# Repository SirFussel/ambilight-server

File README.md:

# Custom Ambilight using Raspberry Pi 3
## Hardware
- Raspberry Pi 3 or higher
- USB framegrabber
- WS2801 LED stripes
- HDPC compatible HDMI splitter
- Power supply
- Wires and cables
## Software
- Hyperion
## Additional Features
- Temperature controlled case using fan
- Blind service to disable the stripes when TV is off
## Pi Configuration
### WIFI configuration
1. Add following lines to ```/etc/network/interfaces``` in order to disable WIFI power save mode:
    ```
    allow-hotplug wlan0
    iface wlan0 inet manual
    post-up iw wlan0 set power_save off
    ```
2. Make sure ```/etc/wpa_supplicant/wpa_supplicant.conf``` looks similar to this and replace the placeholders:
    ```
    ctrl_interface=DIR=/var/run/wpa_supplicant GROUP=netdev
    update_config=1
    country=DE

    network={
            ssid="<ssid>"
            psk="<password>"
    }
    ```
    You can do this by using ```sudo wpa_passphrase "<ssid>" "<password>" >> /etc/wpa_supplicant/wpa_supplicant.conficant.conf``` instead of manually adding it to the file.
3. Restart WIFI by using ```sudo ifconfig wlan0 down``` and ```sudo ifconfig wlan0 up``` afterwards.
### Add services
1. Add a file to ```/etc/systems/system/``` folder and make sure its extension is ```.service```. Its content looks similar to:
    ```
    [Unit]
    Description=Temperature control service
    After=multi-user.target
    [Service]
    Type=simple
    Restart=always
    ExecStart=/usr/bin/python3 /home/pi/tempcontrol.py
    [Install]
    WantedBy=multi-user.target
    ```
2. Register the service using ```sudo service enable <servicename>.service```
3. Run the service using ```sudo service start <servicename>.service```

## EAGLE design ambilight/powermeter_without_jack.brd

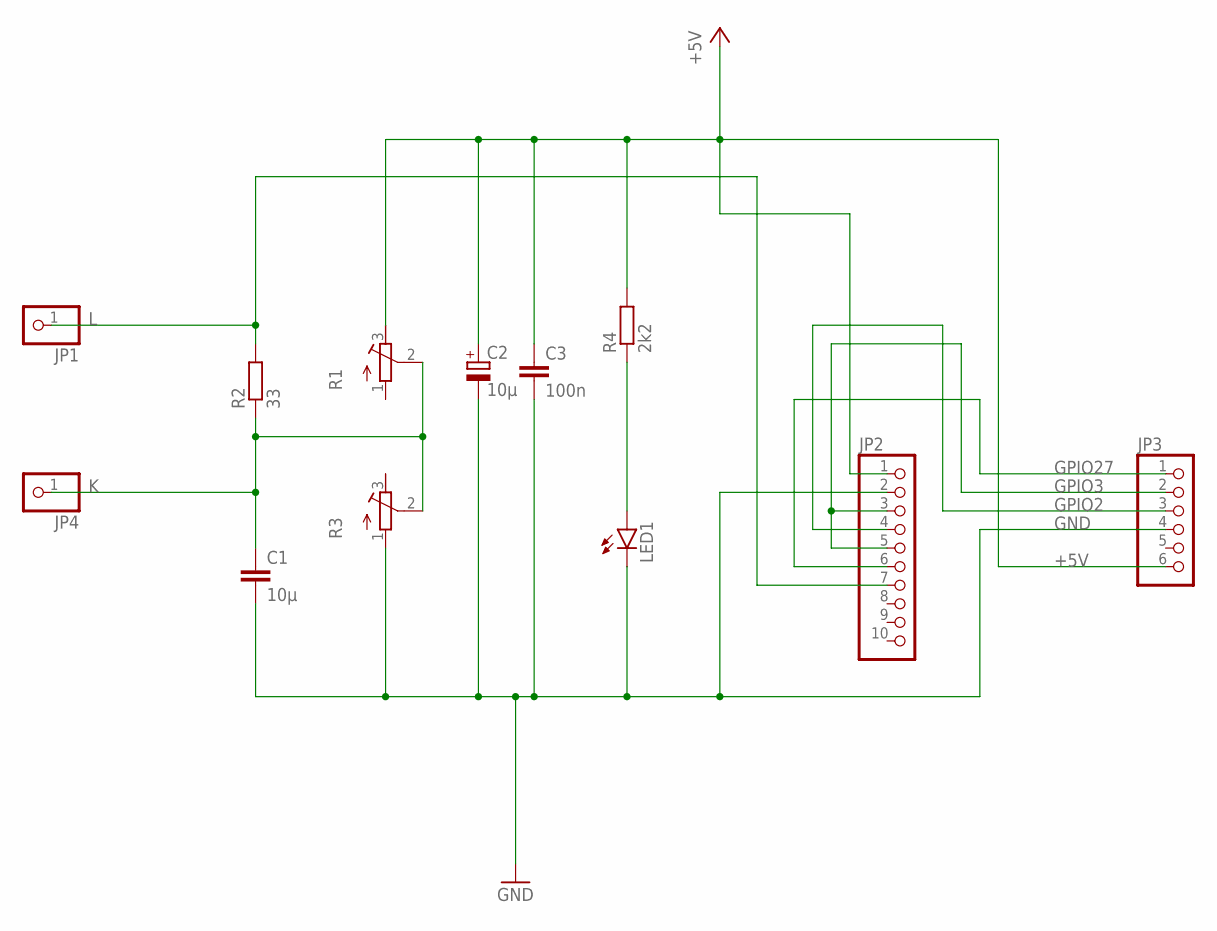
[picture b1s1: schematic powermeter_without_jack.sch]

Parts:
C1: 10µ; C075-052X106
C2: 10µ; E5-5
C3: 100n; C050-025X075
JP1, JP4: PINHD-1X1; 1X01
JP2: PINHD-1X10; 1X10
JP3: PINHD-1X6; 1X06
LED1: LED3MM
R1, R3: R-TRIMM3296W; RTRIM3296W
R2: 33; 0411/15
R4: 2k2; 0207/10

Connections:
+5V: C2.+, C3.1, JP2.1, JP3.6, R1.3 (E), R4.2
GND: C1.2, C2.-, C3.2, JP2.2, JP3.4, LED1.K (C), R3.1 (A)
GPIO2: JP2.4, JP3.3
GPIO3: JP2.3, JP2.5, JP3.2
GPIO27: JP2.6, JP3.1
K: C1.1, JP4.1, R1.2 (S), R2.1, R3.2 (S)
L: JP1.1, JP2.7, R2.2
unnamed: LED1.A, R4.1

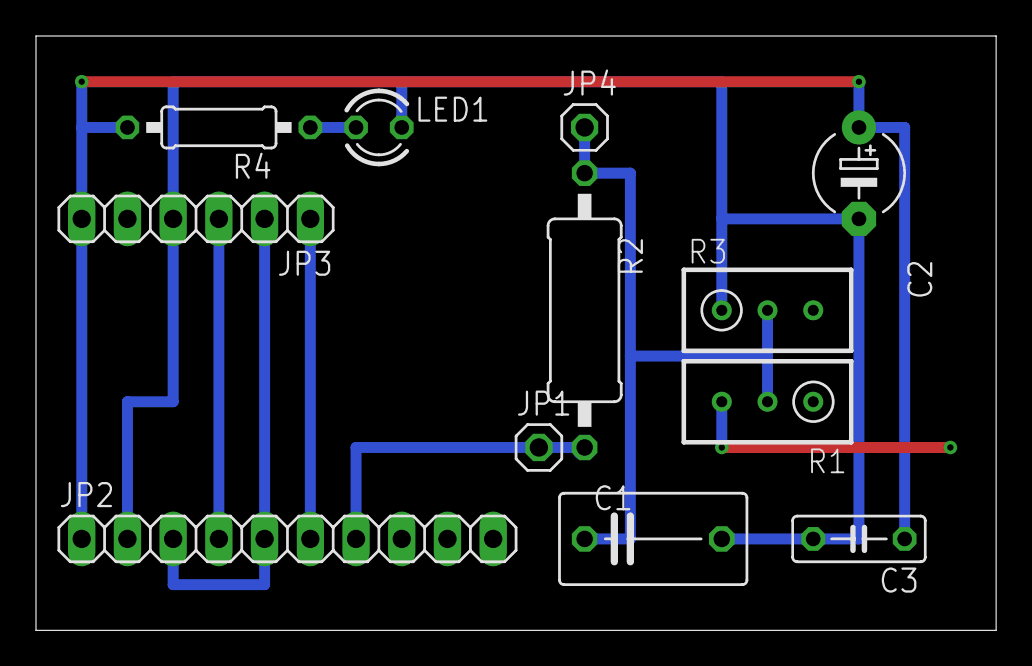
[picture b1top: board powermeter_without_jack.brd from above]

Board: 2 copper layers, 53.3 x 33.0 mm, 12 parts (0 on the bottom side), 8 nets.

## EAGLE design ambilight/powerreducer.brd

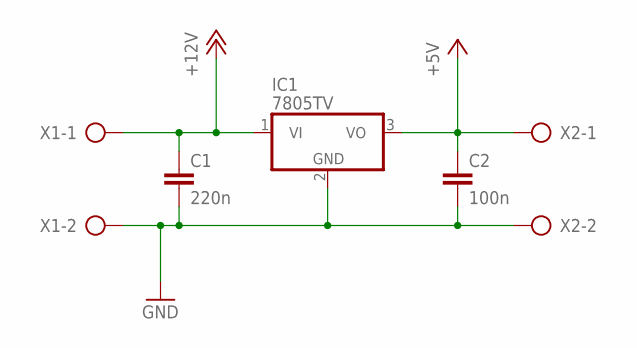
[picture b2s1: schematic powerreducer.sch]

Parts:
C1: 220n; C050-025X075
C2: 100n; C050-025X075
IC1: 7805TV; TO220V
X1, X2: AK300/2

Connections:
+5V: C2.1, IC1.3 (VO), X2.1
+12V: C1.1, IC1.1 (VI), X1.1
GND: C1.2, C2.2, IC1.2 (GND), X1.2, X2.2

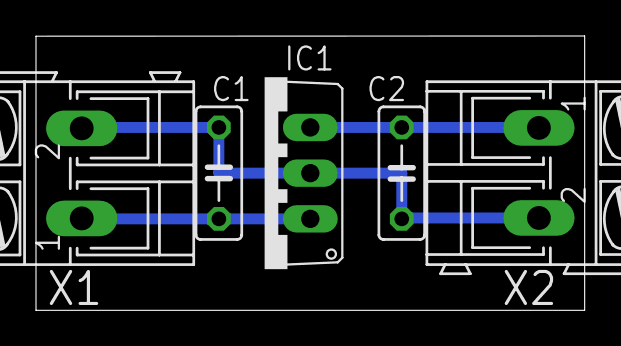
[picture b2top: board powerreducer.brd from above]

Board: 2 copper layers, 30.5 x 15.2 mm, 5 parts (0 on the bottom side), 3 nets.

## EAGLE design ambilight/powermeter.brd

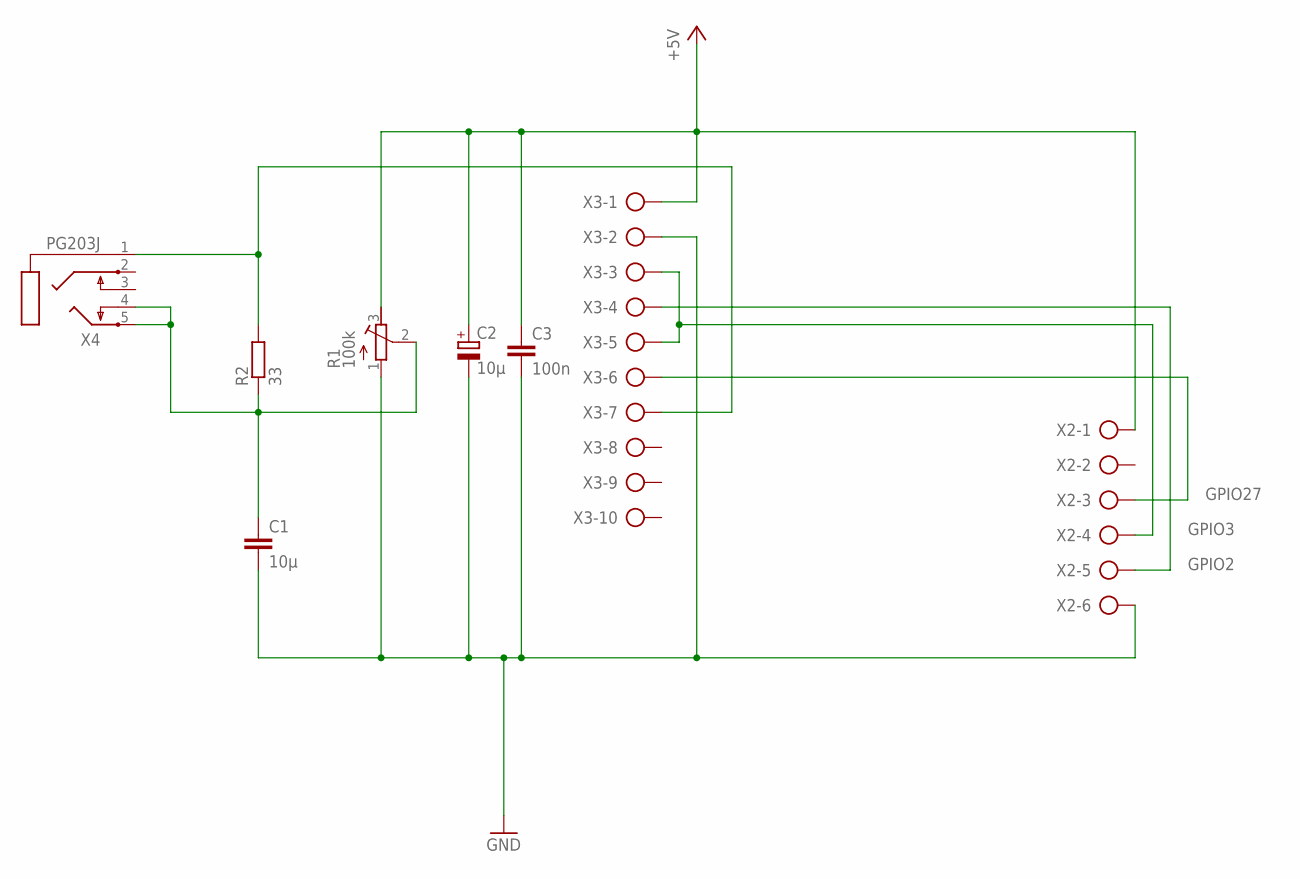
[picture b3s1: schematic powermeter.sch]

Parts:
C1: 10µ; C050-025X075
C2: 10µ; E5-10,5
C3: 100n; C050-025X075
R1: 100k; RTRIM64W
R2: 33; 0309/12
X2: AK300/6
X3: AK300/10
X4: PG203J

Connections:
+5V: C2.+, C3.1, R1.3 (E), X2.1, X3.1
GND: C1.2, C2.-, C3.2, R1.1 (A), X2.6, X3.2
GPIO2: X2.5, X3.4
GPIO3: X2.4, X3.3, X3.5
GPIO27: X2.3, X3.6
unnamed: R2.2, X3.7, X4.1
unnamed: C1.1, R1.2 (S), R2.1, X4.4, X4.5

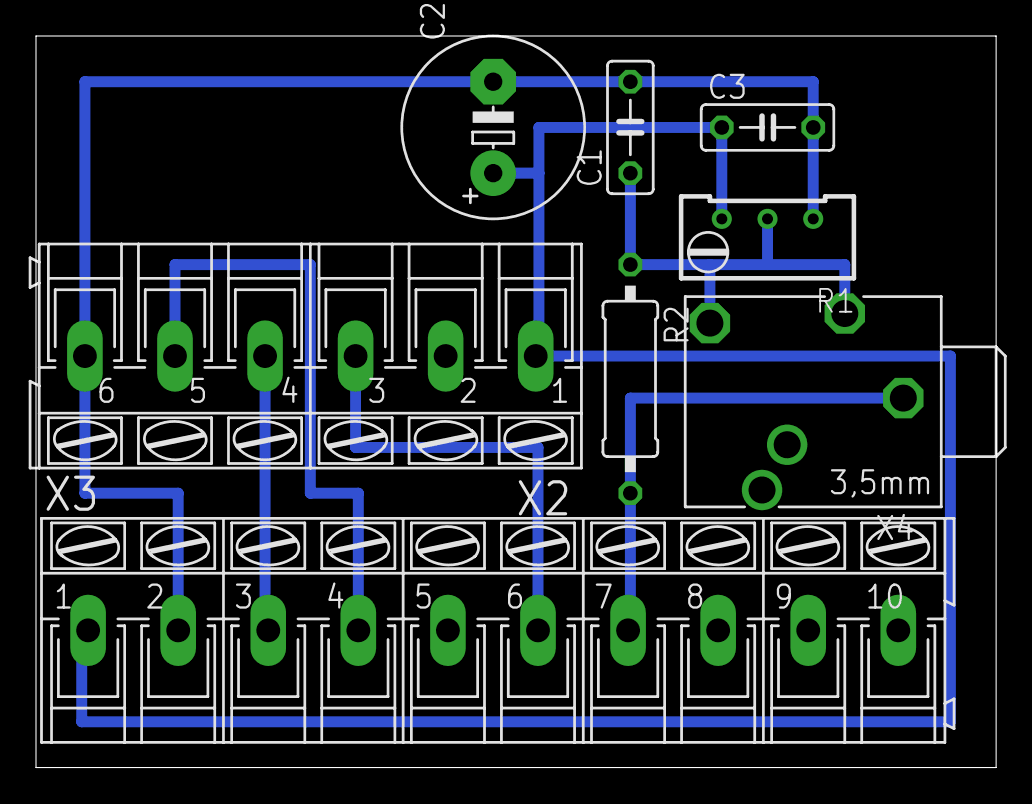
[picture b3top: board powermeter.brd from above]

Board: 2 copper layers, 53.3 x 40.6 mm, 8 parts (0 on the bottom side), 7 nets.

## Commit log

2022-10-01 Added temp control and blind service
2022-10-01 Added source of code fragment
2022-10-02 Restructuring
2022-10-02 Restructured again
2022-10-02 Disabled fan on startup
2022-10-02 Made update and install script generic
2022-10-14 Added pihole config after rename
2024-01-08 Added new technique to check the TVs power status
